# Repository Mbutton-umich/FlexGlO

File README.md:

---
title: FlexGlO Initial Setup
description: See my new project!
---
<head>
  <!-- KaTeX CSS for styling -->
  <script type="text/javascript" async
    src="https://cdnjs.cloudflare.com/ajax/libs/mathjax/2.7.7/MathJax.js?config=TeX-MML-AM_CHTML">
  </script>
</head>

<div style="background-color: #f8f9fa; padding: 10px; text-align: center; border-bottom: 1px solid #ddd;">
  <p style="margin: 0; font-size: 14px; color: grey; font-style: italic;">
    Co-Designers:
    Matt (<a href="https://github.com/Mbutton-umich" style="color: blue; text-decoration: none;">Mbutton-umich</a>),
    Ernesto (<a href="https://github.com/ernestogomezs" style="color: blue; text-decoration: none;">ernestogomezs</a>),
    Pablo (<a href="https://github.com/pgaracu" style="color: blue; text-decoration: none;">pgaracu</a>),
    Sammy (<a href="https://github.com/dana" style="color: blue; text-decoration: none;">GitHub</a>), and
    Youssouf (<a href="https://github.com/eve" style="color: blue; text-decoration: none;">GitHub</a>)
  </p>
</div>

<div style="text-align: center; margin-top: 10px; margin-bottom: 20px;">
  <p style="font-size: 16px; font-weight: bold; color: black;">
    {<a href="https://github.com/example-code" style="color: blue; text-decoration: none;">THE CODE</a> |
    <a href="#implementation-section" style="color: blue; text-decoration: none;">SKIP TO IMPLEMENTATION</a> |
    <a href="#special-thanks-section" style="color: blue; text-decoration: none;">SPECIAL THANKS</a>}
  </p>
</div>

<div style="display: flex; align-items: center; gap: 20px; margin-bottom: 20px;">
  <!-- Text Section -->
  <div style="flex: 2;">
    <h1>What is <span style="color:#39FF14;">FlexGl</span><span style="color:#FF073A;">O</span>?</h1>
    <p>
      Imagine a shirt that transforms your body into a living canvas of motion and energy.  
      This isn't just a garment—it's a gateway to visualizing the power within. Using cutting-edge <strong>EMG (electromyography)</strong> sensors strategically placed across key upper-body muscle groups, this innovative shirt detects even the subtlest electrical signals generated by muscle activation.  
      The result? A spectacular symphony of light, brought to life by vibrant <strong>LEDs</strong>, dynamically illuminating your movements in real-time. Witness the light of your own heart pulse on your chest, captured via <strong>EKG (electrocardiogram)</strong>.
    </p>
  </div>
  <!-- GIF Section -->
  <div style="flex: 1; text-align: center;">
    
    <p style="font-style: italic; margin-top: 8px;">
    Fig. I: <span style="color: #39FF14;">FlexGl</span><span style="color: #FF073A;">O</span> in Action.
    </p>
  </div>
</div>
### Why <span style="color:#39FF14;">FlexGl</span><span style="color:#FF073A;">O</span>?

Are you cheating on your curls? Now we can see that you are. Quantify muscle imbalances or movement weaknesses as **5 BLE nodes** collect data across the body for rehab or performance purposes. Fitness analytics at the speed of light. Are you giving maximum effort in every rep? Simply glance at your mobile device to see the voltage output and muscle activity in real-time.

### Features
- **Precision EMG Monitoring**: Sense the electrical activity of your biceps, triceps, pectorals, deltoids, and more, translating your strength into a visual spectacle.
- **Precision EKG Monitoring**: View the beating of your own heart as you proceed with your workout.
- **Dynamic Illumination**: LED strips glow and shift in intensity, providing an electrifying display of muscle engagement that mirrors your every move.
- **Seamless Integration**: Lightweight, flexible design ensures complete freedom of movement, whether you’re powering through a workout or performing on stage.
- **Washable and Durable Construction**: Features 5 removable BLE nodes for effortless cleaning and maintenance.
- **Customizable Visuals**: Choose from color gradients, patterns, or animations to suit your preferences and mood.

<div style="display: flex; align-items: center; justify-content: center; margin-bottom: 20px;">
  <!-- Phrase Section -->
  <div style="text-align: right; padding-right: 10px;">
    <p style="margin: 0; font-size: 24px; font-style: italic; font-weight: bold; line-height: 1.2; color: #333;">
      STRENGTH<br>ILLUMINATED
    </p>
  </div>

  <!-- Logo Section -->
  <div>
    
  </div>
</div>

<div style="display: flex; align-items: center; justify-content: space-between; border-bottom: 1px solid #ddd; padding-bottom: 20px; margin-bottom: 20px;">
  <div style="flex: 1; text-align: center; padding-right: 10px; border-right: 1px solid #ccc;">
    
  </div>
  <div style="flex: 1; text-align: center; padding: 0 10px; border-right: 1px solid #ccc;">
    
  </div>
  <div style="flex: 1; text-align: center; padding-left: 10px;">
    
  </div>
</div>

<p style="text-align: center; font-style: italic; margin-top: 10px;">
  Fig. II: <span style="color: #39FF14;">FlexGl</span><span style="color: #FF073A;">O</span> Muscle Shirt in Action.
</p>
<div id="implementation-section" style="text-align: left; margin-top: 40px; margin-bottom: 20px;">
  <h1>Implementation Details</h1>
  Sales speak aside we developed this "muscle shirt" over the course of three months and kept our budget to under $1000.00. In this general summary we <strong style="color: blue;">bolded</strong> some key terms if you are interested in tackling similar challenges or projects with similar components.
  <br><br>
  <p>Aquiring muscle signals for EMG and EKG is done using Analog Devices <strong style="color: blue;">AD623</strong> a moderately priced chip that works well for breadboarding because it still comes in a DIP package. The <strong style="color: blue;">single-supply analog filters</strong> all utilize <strong style="color: blue;">TLV246X</strong> chips from Texas Instruments (TI) which again come in DIP packages and are well supported by TI's simple SPICE simulator and filter design widget. We selected <strong style="color: blue;">ESP32-S3 WROOM 1</strong> as the platform for the project for several reasons: the module's integrated antenna, the dual core, and its support and ubiquity amongst hobbyists. All of the code was developed in <strong style="color: blue;">Arduino IDE</strong> in <strong style="color: blue;">embedded C</strong> utilizing <strong style="color: blue;">FreeRTOS</strong> and <strong style="color: blue;">hardware timers</strong> for strict scheduling. The eventual PCBs were created in <strong style="color: blue;">KiCad</strong>. We use <strong style="color: blue;">multi-channel continuous reads over DMA (direct memory access)</strong> to sample up to three muscles at once at every node. That information is then aggregated and processed quickly to be displayed in <strong style="color: blue;">realtime</strong> with quick updates to <strong style="color: blue;">WS2813 LED strips</strong> using the <strong style="color: blue;">FastLED library</strong>. We also quickly send updates to a <strong style="color: blue;">Flutter</strong> mobile application from all five nodes across the upper body. This app allows users to view muscle activation across the whole upper body, or to zoom in and see a live oscilloscope-style view of any particular muscle. From the app, you can also change the LED colors or log data for later analysis. At the tail end of the project, we also tried to do some movement identification once data is collected at the app in <strong style="color: blue;">Dart</strong> using some binary matrix manipulations.
  
  <h2 style="margin-left: 20px; font-style: italic;">Analog Acquisition</h2>

  <div style="display: block; padding-bottom: 20px;">
    <!-- Left side: First paragraph -->
    <p style="padding-left: 20px;">
      We use an Analog Devices instrumentation amplifier AD623 as the pre-Amp phase to extract muscle signals off of the surface of the skin. As you flex a given muscle neurons are firing a ripple of activation signals along the muscle fibers that propogate out to the surface of the skin. With a high impedance differential amplifier we can measure the differnce in voltage between two close points and quantify that activation energy. Under the shirt, users need to put roughly 30 Red Dot Electrodes that button nicely into our electrode snaps and feed into each node via 2.5 mm TRRS (AUX) jacks. It took a lot of testing to select the correct gain resistor for EMG and EKG. We initially used a potentiometer to dial in the correct gain for our purposes; unfortunately, we found the resistance on the breadboard to be pretty finicky and unstable. For the PCB, we landed on 300&Omega; for the EMG and 100&Omega; for the EKG circuit. These minscule muscle activation signals are in the range [50&mu;V, 30mV] for EMG and [500&mu;V, 5mV] for EKG. We needed strike a balance and select a gain that is large enough to bring these voltages into the full range of our ADC ([0, 3.3]V) but not so large that upon activation we get instant saturation. From the AD623 datasheet that places our selected gains at:
    </p>
      <div style="text-align: center; margin-top: 30px;">
        $$
          R_G = \frac{100\, \text{k}\Omega}{G - 1} \implies G = 1 + \frac{100\, \text{k}\Omega}{R_G} \implies 
          \left\{
            \begin{array}{l}
              G_{EMG} = 1 + \frac{100\, \text{k}\Omega}{300 \, \Omega} = 334.33 \\
              G_{EKG} = 1 + \frac{100\, \text{k}\Omega}{100 \, \Omega} = 1000
            \end{array}
          \right.
        $$
      </div>
      <p style="padding-left: 20px;"> 
      From the jump, we also wanted to avoid the dual-supply setup we saw on a lot of online EXG tutorials. So we used a voltage divider at the reference pin to bump negative muscle signals into the [0, 3.3]V range within the rails. For the entire analog design process, we relied heavily on TI's <a href="https://webench.ti.com/filter-design-tool/filter-type" style="color: blue;">Filter Design Tool</a> and made sure to scale things to the most common ceramic capacitor and resistor sizes where possible.
    </p>
    
    <!-- Bullet list and paragraph placed under the first paragraph -->
    <p style="padding-left: 20px;">There were also three other TI "Application Reports" that were super helpful <em>especially the last one</em> which explicitly shows how to modify things for single-supply:</p>
    <ul style="text-align: left; margin-top: 10px; padding-left: 120px;">
      <li><a href="https://www.ti.com/lit/an/sloa024b/sloa024b.pdf" style="color: blue;">Analysis of Sallen-Key Architecture</a></li>
      <li><a href="https://www.ti.com/lit/an/sloa030a/sloa030a.pdf" style="color: blue;">Single-Supply Op Amp Design Techniques</a></li>
      <li><a href="https://www.ti.com/lit/an/sloa096/sloa096.pdf" style="color: blue;">More Filter Design on a Budget</a></li>
    </ul>
  </div>
  <div>
       <p style="padding-left: 20px;">
      After the instrumentation amp the boosted signal proceeds through a series of filter stages. For the EMG we use a Sallen-Key Low Pass followed by a Sallen-Key High Pass filter to create a bandpass and extract relevant EMG frequencies in the range [5, 500]Hz. After the bandpass the the final stage is a two amp Fleige Notch Filter to remove 60Hz interference which was very prevalent in the lab where we did most of our testing. The EMG filter architecture is shown below using a rail-to-rail quad-amp TLV2464 IC from TI (and the EKG schematic is in the Git):
    </p>
  </div>
    <div style="text-align: center; margin-top: 30px;">
    
    <p style="font-style: italic; margin-top: 8px; text-align: center;">
      Fig. V: The EMG filter schematic.
    </p>
  </div>

  <div style="display: flex; justify-content: space-between; align-items: flex-start;">
    <div style="flex: 1; padding-right: 20px;">
      <p style="padding-left: 20px;">
        The EKG circuit is similar to the EMG with just changes to the electrode placement and the filter passives to bring the frequency range within [0.2, 200]Hz. After their conception, we used TINA (TI's Interactive Network Analyze) to simulate both the EKG and EMG circuits. To the right is an ad-hoc sweep of the EMG filter to make sure the bandpass cutoffs are about right. TINA was pretty useful because we had at least some assurance that the circuit would work before ever ordering parts. We also got a nice frequency response plot of the circuit. In simulation for example, we could tune the depth and width of the 60Hz notch by playing with the values of the R_M_O# pair of resistors in the schematic.
        
      </p>
    </div>
    
    <!-- Right side: Image and caption -->
    <div style="text-align: right; max-width: 100%; display: inline-block;">
      
    </div>
  </div>

<div>
  <p style="font-style: italic; margin-top: 8px; text-align: center; max-width: 100%; word-wrap: break-word;">
    Fig. IV: [Right] TINA Simulator Oscilloscope showing the response of the full EMG filter at different frequencies.<br>[Bottom] Bode Plot of showing filter magnitude and phase.
  </p>
  </div>
  <div>
    <p style="padding-left: 20px;">
    After all that simulation we purchased through-hole parts to build the circuit in breadboard form. For uniformity we stuck with Yageo for resitors and Kemet for capacitors maintaining &le;5% tolerances to keep the circuit realization close to the simulations. The EMG breadboard worked without issue despite the tangled mess of the Notch filter on the small breadboard.
    <br><br>
    However our EKG proved more challenging as the signal was very weak when we used the canonical three-lead electrode placement from SENIAM (Surface ElectroMyoGraphy for the Non-Invasive Assessment of Muscles). At maximum gain the heartbeat was still almost too faint to be recognized by the ADC. Also moving your leg, breathing, or flexing your chest would drag the signal all around. A great link: <a href="https://www.aclsmedicaltraining.com/blog/guide-to-understanding-ecg-artifact/" style="color: blue; text-decoration: none;">Guide to Understanding ECG Artifact</a>, allowed us to understand we were witnessing a "wandering baseline". To remedy this issue we changed from a bandpass and notch combination to a lone narrow bandpass in the range [0.25, 25]Hz. We also experimented with alternative electrode placement to obtain a stronger heartbeat signal. After trying a F-EKG three-lead constellation with placement on the sternum and lower left rib we had better results. This electrode constellation captures the "&epsilon;-Wave" as opposed to the "R-Wave" and it just worked better for our purposes of capturing a BPM.
    </p>
  </div>
  <div style="display: flex; align-items: center; justify-content: space-between; border-bottom: 1px solid #ddd; padding-bottom: 20px; margin-bottom: 20px;">
  <!-- First GIF -->
  <div style="flex: 1; text-align: center; padding-right: 10px; border-right: 1px solid #ccc;">
    
  </div>

  <!-- Second GIF -->
  <div style="flex: 1; text-align: center; padding: 0 10px; border-right: 1px solid #ccc;">
    
  </div>

  <!-- Third GIF -->
  <div style="flex: 1; text-align: center; padding-left: 10px;">
    
  </div>
</div>
<p style="text-align: center; font-style: italic; margin-top: 10px;">
  Fig. VI: [Left] EMG analog test with LED output. [Center] EMG I-Amp and Filter Breadboard. [Righ] EKG analog test with LED output.
</p>

<h2 style="margin-left: 20px; font-style: italic;">Digital Sampling and Conditioning</h2>

<div style="display: flex; justify-content: space-between; align-items: center; margin-bottom: 20px;">
  <!-- Left side: Image and caption -->
  <div style="flex: 1; text-align: center;">
    
    <p style="font-style: italic; margin-top: 8px;">Fig. X: Block diagram of muscle signal sampling and conditioning.</p>
  </div>

  <!-- Right side: Text content -->
  <div style="flex: 1; padding-left: 20px;">
    <p>
      After all the hard work aquiring and cleaning the muscle signals we eventually pass them through the ESP32-S3's ADC and into the digital domain. Recall that each node has at most three muscles (EMG0, EMG1, and EKG), so initally we were doing single shot conversions for three channels. Also recall that EMG is in the range [5, 500]Hz so we wanted to sample above the Nyquist rate of 1kHz. As we got closer to 1kHz we found the CPU was overwhelmed with all of the interrupts for sampling all three channels. To reduce the load on the CPU we instead switched to a continuous sampling of three channels over DMA. Although there was example code for continous sampling on a single channel of the ESP32 ADC there was less support for multi-channel sampling via DMA. Fortunately the Expressif documentation was decently clear and after a small struggle we were able to configure the DMA appropriotely. The sampling and signal conditioning process largely follows the block diagram to the left:
      <br><br>
      Everything occurs sequentially on Core 1: DMA fills its buffer which releases the process_ADC FreeRTOS task. After process_ADC finishes the process_LEDs task is released and will display our most recently measured values via the LEDs. And to be clear when I say "released" I mean we use defferred interrupt handling. So a quick interrupt sets a flag that unblocks a task or I explcitly release a task which in FreeRTOS-speak means using <span style="font-family: Consolas, monospace;">xTaskNotifyGive(...)</span>.
      <br><br>
      A few more notes on design decisions. We had to rectify digitally because we made our analog front end single-supply. Normally, with a zero centered signal we could just add a diode bridge at the end of the filters and an RC smoother to rectify the signal. However, with the 1.65V offset single-supply signal we just flip the lower values coming off the ADC. This way we can get a kind of absolute value for muscle activity which is translated into levels once given to the process_LEDs task.
    </p>
  </div>
</div>
  <div>
    <p style="padding-left: 20px;">
    It's also worth noting everything about the conditioning pipeline is parameterized. We experimented with different DMA buffer sizes and the subsequent median filter window lengths. Again from testing we had to strike a balance: if the filter window is too long we flatten away brief moments of muscular exertion and its difficult to max out the LED bar; if we make it too short we don't smooth out the divots from rectification and the LEDs look very flickery and faint. Also if you make the buffer too big we produce a median at a rate below the Nyquist and allias effects take hold. In the end we selected a window of size 8 at 8kHz DMA. Before switching to DMA we had actually used a moving average filter but with the DMA setup we are collecting data in bunches of full buffers so the median filter (which was more robust against occasional noisy outliers) was a better choice for a similar computational cost.

    Finally, the Arduino serial plotter was a particularly useful tool for debugging all of this ADC code. We could visually inspect how the signals are sampling and rectifying and averaging to make judgments about the qaulity of our signal chain. Although at high sampling frequencies the <span style="font-family: Consolas, monospace;">Serial.print(...)</span> would lag or crash it was a heavily leveraged asset.
    </p>
  </div>
  <div style="text-align: center; margin-top: 30px;">

<p style="font-style: italic; margin-top: 8px; text-align: center;">
Fig. V: Arduino Serial Plotter showing rectification of a 20mV signal at 32Hz.
</p>
</div>

<h2 style="margin-left: 20px; font-style: italic;">Fiber Optics...Muscle Fiber Optics</h2>

<div style="text-align: left; margin-left: 20px;">
  <p>
    We are fully indebted to the FastLED library, which allows us to update the LED bars and the LED circle for the heart pulse. There were basically no problems with the library, and the interfaces are very clean. The only hiccup involved multiple tasks contending for control of RMT assets. In prior projects, we had bit-banged the data lines for these strips, but we were fortunate that FastLED does this and does it efficiently. For the bars, we simply range down the median coming off the ADC and ignite that number of LEDs. For the EKG circle, the actual heart pulse was too quick and looked very faint, so we used some software tricks to give a "stickiness" to the heartbeat to make it more prominent. FastLED uses the RMT (Remote Control Transceiver) peripherals to bit-bang the precise PWM patterns and encode colors to the strips. The ESP32-S3 has 4 transmission RMT channels, so the three strips compute the colors and levels serially and then update in parallel.
  </p>
  <p>
    We also made a nice "start-up pulse" animation (in maize and blue) and a "waiting to connect" animation. Although we developed these initially as flair for the system, they were actually incredibly useful. When debugging, the chip might crash or disconnect, and having those visual cues was a big help.
  </p>
  <p>
    For the final system on the PCB, we also measured the FPS (frames per second) for all the LEDs updating. We fall within [110, 150] FPS for regular operation. We selected WS2813 strips in particular for several reasons:
  </p>
</div>

<div>
  <ul style="padding-left: 120px; margin-top: 10px;">
    <li>The dual redundant data lines are good if a cable breaks during regular exercise.</li>
    <li>The refresh rate is limited by the 280 ns reset time, allowing faster strip updates over the cheaper WS2812B variety.</li>
    <li>For small strips, the 5V source voltage can be satisfied with only 3.3V.</li>
  </ul>
</div>

<div style="text-align: left; margin-left: 20px;">
  <p>
    That last point was a particular concern for us because we are running the sensor nodes off of a 3.7V lithium battery and stepping things down further via an LDO to 3.3V. We probably should have included a level shifter, but it would have taken up space on our board. Luckily, after testing on the development breadboard, even the 12 LED circle strip lit up without turning red or fading at only 3.3V.
  </p>
</div>

<div style="display: flex; align-items: center; justify-content: space-between; border-bottom: 1px solid #ddd; padding-bottom: 20px; margin-bottom: 20px;">
  <div style="flex: 1; text-align: center; padding-right: 10px; border-right: 1px solid #ccc;">
    
  </div>
  <div style="flex: 1; text-align: center; padding: 0 10px; border-right: 1px solid #ccc;">
    
  </div>
  <div style="flex: 1; text-align: center; padding-left: 10px;">
    
  </div>
</div>

<p style="text-align: center; font-style: italic; margin-top: 10px;">
  Fig. II: <span style="color: #39FF14;">FlexGl</span><span style="color: #FF073A;">O</span> Muscle Shirt in Action.
</p>

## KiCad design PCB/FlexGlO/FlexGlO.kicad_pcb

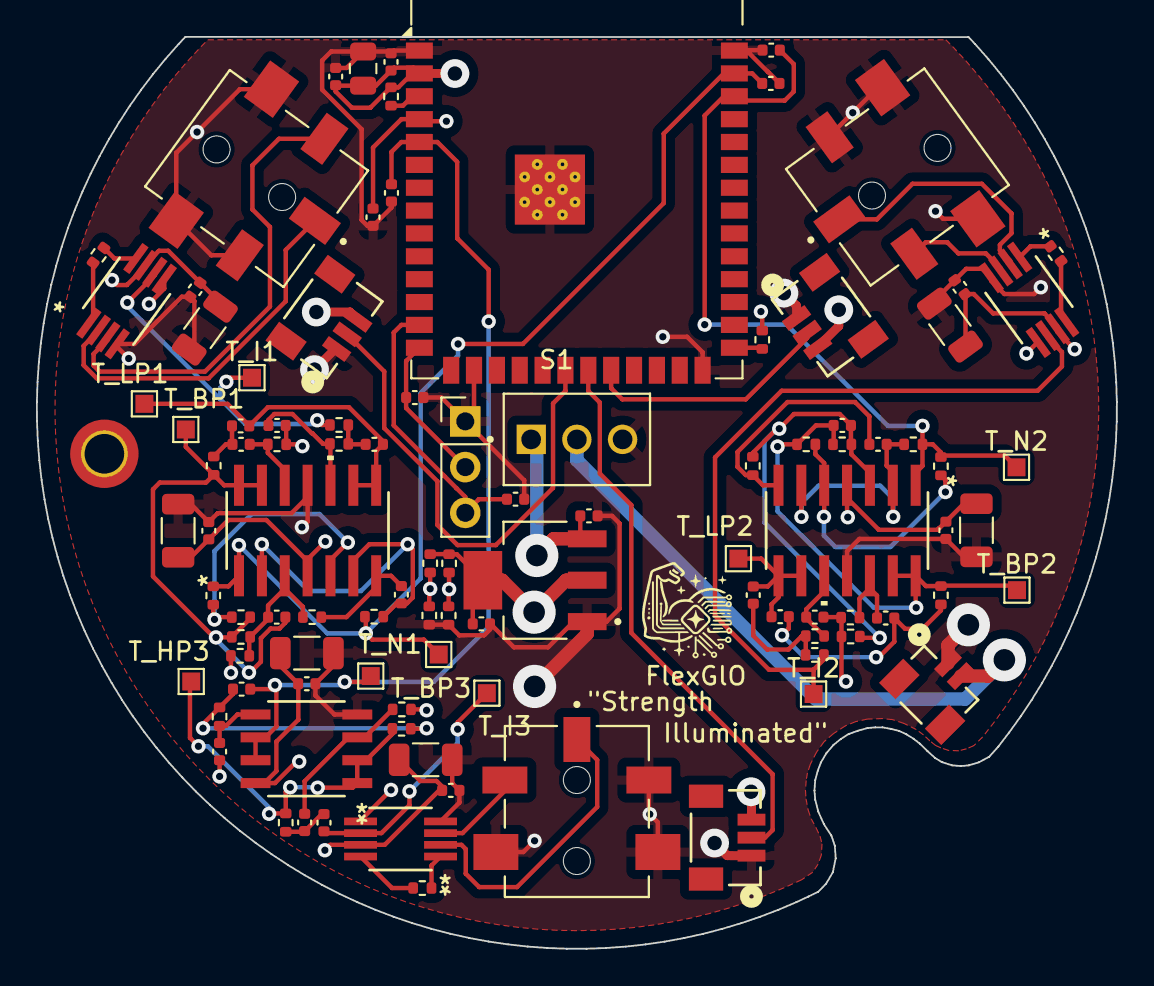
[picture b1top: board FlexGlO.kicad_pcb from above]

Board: 4 copper layers, 60.0 x 50.7 mm, 101 parts (0 on the bottom side), 56 nets.

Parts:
C_ADC_F1, C_ADC_F2, C_ADC_F3, C_ADC_F4: CL05B104KO5NNNC; C_0402_1005Metric
C_ESP_D1: CL05B104KO5NNNC; C_0402_1005Metric
C_ESP_D2: CL21A226MAQNNNE; C_0805_2012Metric
C_ESP_D3: CL05A105KP5NNNC; C_0402_1005Metric
C_ESP_USB1, C_ESP_USB2: 0402CG220J500NT; C_0402_1005Metric
C_I_D1, C_I_D3, C_I_D5: CL05B104KO5NNNC; C_0402_1005Metric
C_I_D2, C_I_D4, C_I_D6: TAJA106K016RNJ; C_1206_3216Metric
C_K_D1: CL05B104KO5NNNC; C_0402_1005Metric
C_K_D2: T491A685K016AT; C_1206_3216Metric
C_K_H1, C_K_H2: CL05A105KP5NNNC; C_0402_1005Metric
C_K_L1: CL05A474KP5NNNC; C_0402_1005Metric
C_K_L2: CL05A334KA5NNNC; C_0402_1005Metric
C_LDO1, C_LDO2: CL05A105KP5NNNC; C_0402_1005Metric
C_M_D1, C_M_D3: CL05B104KO5NNNC; C_0402_1005Metric
C_M_D2, C_M_D4: T491A685K016AT; C_1206_3216Metric
C_M_H1, C_M_H2, C_M_H3, C_M_H4: CL05A105KP5NNNC; C_0402_1005Metric
C_M_L1, C_M_L3: CL05B224KO5NNNC; C_0402_1005Metric
C_M_L2, C_M_L4: CL05B104KO5NNNC; C_0402_1005Metric
C_M_O1, C_M_O2, C_M_O3, C_M_O4: CL05A105KP5NNNC; C_0402_1005Metric
DUAL_AMP1: TLV2462AIDR; D8-M
ESP1: ESP32-S3-WROOM-1
H1: MountingHole; MountingHole_2.2mm_M2_ISO14580_Pad_TopBottom
I_AMP1, I_AMP2, I_AMP3: AD623ARMZ; RM_8_ADI-M
JACK1, JACK2, JACK3: SJ1-42534-SMT-TR; CUI_SJ1-42534-SMT-TR
JST_2P1: BM02B-SRSS-TB LFSN; CONN_BM02B-SRSS-TB_JST
JST_3P1, JST_3P2, JST_3P3: BM03B-SRSS-TBLFSN; CONN_BM03B-SRSS-TBLFSN_JST
LDO1: TLV1117LV33DCYR; VREG_TLV1117LV33DCYR
QUAD_AMP1, QUAD_AMP2: TLV2464CDR; D14-M
R_ESP_PU1, R_ESP_PU4: 0402WGF1002TCE; R_0402_1005Metric
R_F_D1, R_F_D2: 0402WGF1002TCE; R_0402_1005Metric
R_I_D1, R_I_D2: 0402WGF1003TCE; R_0402_1005Metric
R_I_G1, R_I_G2: RC0402FR-07300RL; R_0402_1005Metric
R_I_G3: RC0402FR-07100RL; R_0402_1005Metric
R_K_H1: RC0402FR-07549KL; R_0402_1005Metric
R_K_H2: RC0402FR-07732KL; R_0402_1005Metric
R_K_L1: RC0402FR-0741K2L; R_0402_1005Metric
R_K_L2: RC0402FR-0788K7L; R_0402_1005Metric
R_M_H1, R_M_H3: RC0402FR-0721KL; R_0402_1005Metric
R_M_H2, R_M_H4: RC0402FR-0745K3L; R_0402_1005Metric
R_M_L1, R_M_L3: RC0402FR-071K5L; R_0402_1005Metric
R_M_L2, R_M_L4: 0402WGF1501TCE; R_0402_1005Metric
R_M_N1, R_M_N2, R_M_N3, R_M_N4: 0402WGF1003TCE; R_0402_1005Metric
R_M_O1, R_M_O2, R_M_O3, R_M_O4: RC0402FR-072K61L; R_0402_1005Metric
R_M_Q1, R_M_Q2, R_M_Q3, R_M_Q4: 0402WGF1002TCE; R_0402_1005Metric
S1: 200MSP1T2B4M2QE; SW_200MSP1T2B4M2QE
T_BP1, T_BP2, T_BP3: TestPoint; TestPoint_Pad_1.0x1.0mm
T_HP3: TestPoint; TestPoint_Pad_1.0x1.0mm
T_I1, T_I2, T_I3: TestPoint; TestPoint_Pad_1.0x1.0mm
T_LP1, T_LP2: TestPoint; TestPoint_Pad_1.0x1.0mm
T_N1, T_N2: TestPoint; TestPoint_Pad_1.0x1.0mm
USB_RAW1: USB_RAW; PinHeader_1x03_P2.54mm_Vertical

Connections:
+3.3V: C_ESP_D1.1, C_ESP_D2.2, C_ESP_D3.2, C_I_D1.1, C_I_D2.1, C_I_D3.1, C_I_D4.1, C_I_D5.1, C_I_D6.1, C_K_D1.2, C_K_D2.1, C_LDO2.1, C_M_D1.2, C_M_D2.1, C_M_D3.2, C_M_D4.1, DUAL_AMP1.8 (VDD+), ESP1.2 (3V3), I_AMP1.7 (Vs+), I_AMP2.7 (Vs+), I_AMP3.7 (Vs+), JST_3P1.3, JST_3P2.3, JST_3P3.3, LDO1.2 (OUT_2), LDO1.4 (OUT_4), QUAD_AMP1.4 (VDD+), QUAD_AMP2.4 (VDD+), R_ESP_PU1.2, R_ESP_PU4.1, R_F_D1.1, R_I_D1.1
/ESP1/BOOT1: ESP1.27 (IO0), R_ESP_PU4.2
/ESP1/D+_G: C_ESP_USB1.1, ESP1.13 (IO19), USB_RAW1.3
/ESP1/EN: ESP1.3 (EN), R_ESP_PU1.1
/amp_phase1/E+: I_AMP1.3 (+), JACK1.3
/amp_phase1/E-: I_AMP1.2 (-), JACK1.1
/amp_phase2/E+: I_AMP2.3 (+), JACK2.3
/amp_phase2/E-: I_AMP2.2 (-), JACK2.1
/amp_phase3/E+: I_AMP3.3 (+), JACK3.3
/amp_phase3/E-: I_AMP3.2 (-), JACK3.1
/power_reference1/BAT_+3.7V: JST_2P1.2, S1.2
AMP_OUT1: I_AMP1.6, R_M_L1.2, T_I1.1
AMP_OUT2: I_AMP2.6, R_M_L3.2, T_I2.1
AMP_OUT3: C_K_H1.1, I_AMP3.6, T_I3.1
BONE_REF: C_ADC_F1.1, C_ADC_F2.1, C_ADC_F3.1, C_ADC_F4.1, C_ESP_D1.2, C_ESP_D2.1, C_ESP_D3.1, C_ESP_USB1.2, C_ESP_USB2.2, C_I_D1.2, C_I_D2.2, C_I_D3.2, C_I_D4.2, C_I_D5.2, C_I_D6.2, C_K_D1.1, C_K_D2.2, C_LDO1.2, C_LDO2.2, C_M_D1.1, C_M_D2.2, C_M_D3.1, C_M_D4.2, DUAL_AMP1.4 (GND), ESP1.1 (GND), ESP1.16 (IO46), ESP1.26 (IO45), ESP1.40 (GND), ESP1.41 (GND), I_AMP1.4 (Vs-), I_AMP2.4 (Vs-), I_AMP3.4 (Vs-), JACK1.2, JACK1.4_1, JACK1.4_2, JACK2.2, JACK2.4_1, JACK2.4_2, JACK3.2, JACK3.4_1, JACK3.4_2, JST_2P1.1, JST_3P1.1, JST_3P2.1, JST_3P3.1, LDO1.1 (GND), QUAD_AMP1.11 (GND), QUAD_AMP2.11 (GND), R_F_D2.2, R_I_D2.2, S1.3, USB_RAW1.1
F_EKG1: C_ADC_F4.2, C_K_L1.1, DUAL_AMP1.6 (2IN-), DUAL_AMP1.7 (2OUT), ESP1.5 (IO5), T_BP3.1
F_EMG1: C_ADC_F1.2, ESP1.39 (IO1), QUAD_AMP1.1 (1OUT), R_M_N2.2, R_M_O2.1, T_N1.1
F_EMG2: C_ADC_F2.2, ESP1.38 (IO2), QUAD_AMP2.1 (1OUT), R_M_N4.2, R_M_O4.1, T_N2.1
LED_DATA1: ESP1.20 (IO12), JST_3P1.2
LED_DATA2: ESP1.22 (IO14), JST_3P2.2
LED_DATA3: ESP1.21 (IO13), JST_3P3.2
unnamed: C_K_H1.2, C_K_H2.2, R_K_H1.1
unnamed: C_K_L1.2, R_K_L1.1, R_K_L2.2
unnamed: C_M_H1.1, C_M_H2.2, R_M_H1.2
unnamed: C_M_H3.2, C_M_H4.1, R_M_H3.2
unnamed: C_M_L1.1, R_M_L1.1, R_M_L2.2
unnamed: C_M_L3.1, R_M_L3.1, R_M_L4.2
unnamed: C_K_H2.1, DUAL_AMP1.3 (1IN+), R_K_H2.1
unnamed: DUAL_AMP1.1 (1OUT), DUAL_AMP1.2 (1IN-), R_K_H1.2, R_K_L1.2, T_HP3.1
unnamed: C_K_L2.1, DUAL_AMP1.5 (2IN+), R_K_L2.1
unnamed: C_ESP_USB2.1, ESP1.14 (IO20), USB_RAW1.2
unnamed: I_AMP1.1 (Rg), R_I_G1.1
unnamed: I_AMP1.8 (Rg), R_I_G1.2
unnamed: I_AMP2.1 (Rg), R_I_G2.1
unnamed: I_AMP2.8 (Rg), R_I_G2.2
unnamed: I_AMP3.1 (Rg), R_I_G3.1
unnamed: I_AMP3.8 (Rg), R_I_G3.2
unnamed: C_LDO1.1, LDO1.3 (IN), S1.1
unnamed: C_M_O1.1, QUAD_AMP1.3 (1IN+), R_M_O1.1, R_M_Q1.2, R_M_Q2.1
unnamed: C_M_O2.2, QUAD_AMP1.2 (1IN-), QUAD_AMP1.6 (2IN-), R_M_O2.2
unnamed: QUAD_AMP1.5 (2IN+), R_M_N1.2, R_M_N2.1
unnamed: C_M_O2.1, QUAD_AMP1.7 (2OUT), R_M_O1.2
unnamed: C_M_L2.2, QUAD_AMP1.10 (3IN+), R_M_L2.1
unnamed: C_M_H1.2, C_M_L1.2, QUAD_AMP1.8 (3OUT), QUAD_AMP1.9 (3IN-), T_LP1.1
unnamed: C_M_H2.1, QUAD_AMP1.12 (4IN+), R_M_H2.2
unnamed: C_M_O1.2, QUAD_AMP1.13 (4IN-), QUAD_AMP1.14 (4OUT), R_M_H1.1, R_M_N1.1, R_M_Q1.1, T_BP1.1
unnamed: C_M_O3.1, QUAD_AMP2.3 (1IN+), R_M_O3.1, R_M_Q3.2, R_M_Q4.1
unnamed: C_M_O4.2, QUAD_AMP2.2 (1IN-), QUAD_AMP2.6 (2IN-), R_M_O4.2
unnamed: QUAD_AMP2.5 (2IN+), R_M_N3.2, R_M_N4.1
unnamed: C_M_O4.1, QUAD_AMP2.7 (2OUT), R_M_O3.2
unnamed: C_M_L4.2, QUAD_AMP2.10 (3IN+), R_M_L4.1
unnamed: C_M_H4.2, C_M_L3.2, QUAD_AMP2.8 (3OUT), QUAD_AMP2.9 (3IN-), T_LP2.1
unnamed: C_M_H3.1, QUAD_AMP2.12 (4IN+), R_M_H4.2
unnamed: C_M_O3.2, QUAD_AMP2.13 (4IN-), QUAD_AMP2.14 (4OUT), R_M_H3.1, R_M_N3.1, R_M_Q3.1, T_BP2.1
V_F_REF: C_ADC_F3.2, C_K_L2.2, C_M_L2.1, C_M_L4.1, ESP1.4 (IO4), R_F_D1.2, R_F_D2.1, R_K_H2.2, R_M_H2.1, R_M_H4.1, R_M_Q2.2, R_M_Q4.2
V_I_REF: I_AMP1.5 (Ref), I_AMP2.5 (Ref), I_AMP3.5 (Ref), R_I_D1.2, R_I_D2.1

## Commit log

2024-11-19 Create _config.yaml
    GitPages Test
2024-11-19 Create README.md
    Just testing
2024-11-19 Local Server Test
2024-11-19 Building out Pages
2024-11-19 Basic Intro Done
2024-11-19 Added index.html
2024-11-19 Fixed Index
2024-11-19 Fixed Indexing Again
2024-11-19 Fixed again?
2024-11-20 Few Sections Done
    Also setup LateX and have good sense of importing gifs and images
2024-11-20 Updated Index Files
2024-11-20 Updated Pablo Contact
2024-11-20 readme versus index issues
2024-11-22 Fixed filter schem image
2024-11-22 Big Image not loading why?
2024-11-22 image check
2024-11-22 Moved big pic
2024-11-22 Wrong index file?
2024-11-22 correct Index Pushed
2024-11-22 readme works?
2024-11-22 Capitalization matters for images
2024-11-22 LED Section done
    Details about LED stuff
2024-11-22 Resized some gifs
2024-11-22 Power Section Updated
2024-12-03 Updated to PCB Section
2024-12-03 Audio Test
2024-12-03 Audio Attempt Continued
    Link should work for deployment on Git
2024-12-03 Hint for the Audio
2024-12-03 Fixed audio formatting
2024-12-03 Project Itself Added from Ernesto
2024-12-03 Cleared ReadMe to barebones
2024-12-03 Fixed Figure #s and Font Sizes Added Assembly Pics
2024-12-03 Table of Contents working
2024-12-03 Table of Contents and Git Users Updated
2024-12-03 Added PCB and Analog stuff
2024-12-05 Updated Files for the PCB
    PCB files and some edits to filter thresholds to avoid noise
2024-12-05 Spelling Grammar Gitpages
2024-12-05 Spell Check
    Details about the JTAG and spell check
